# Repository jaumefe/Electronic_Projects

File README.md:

# Electronic_Projects
At this file, there will be included some electronic projects which could be used for home automation. Here, we can find the list of projects done until now:
* Weather Forecast Station

## Weather Forecast
It consists of a station which includes two sensors:
* SHT40-AD1B-R2: Temperature and Humidity Sensor
* DPS310: Barometric Pressure Sensor

This project only contains a board with both sensors which should be connected to a MCU by a I2C serial interface. In this case, I will be using a Raspberry Pi Pico to do the project. If you are also interested on the code, please check the following repository: https://github.com/jaumefe/Raspberry_Pico/tree/main/Weather_Forecast

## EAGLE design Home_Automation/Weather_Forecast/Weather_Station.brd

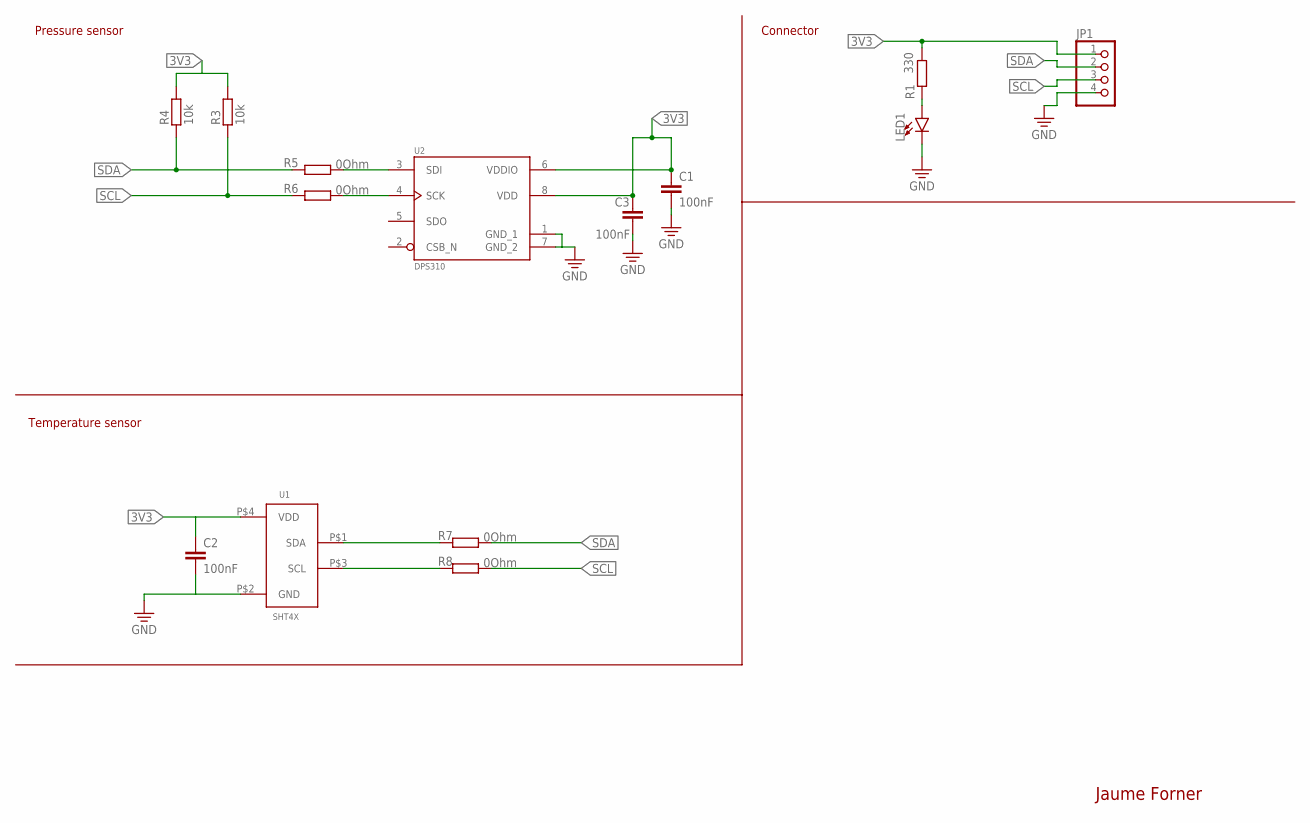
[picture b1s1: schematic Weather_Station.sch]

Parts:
C1, C2, C3: 100nF; C0603K
JP1: PINHD-1X4; 1X04
LED1: LED0603; LED-0603
R1: 330; R0603
R3, R4: 10k; R0603
R5, R6, R7, R8: 0Ohm; R0603
U1: SHT4X; SHT40-SHT41
U2: DPS310; LGA8S145X65P2X4_200X250X110-V

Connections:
3V3: C1.1, C2.1, C3.1, JP1.1, R1.1, R3.2, R4.2, U1.P$4 (VDD), U2.6 (VDDIO), U2.8 (VDD)
GND: C1.2, C2.2, C3.2, JP1.4, LED1.C, U1.P$2 (GND), U2.1 (GND_1), U2.7 (GND_2)
unnamed: R6.1, U2.4 (SCK)
unnamed: R5.1, U2.3 (SDI)
unnamed: R7.2, U1.P$1 (SDA)
unnamed: R8.2, U1.P$3 (SCL)
unnamed: LED1.A, R1.2
SCL: JP1.3, R3.1, R6.2, R8.1
SDA: JP1.2, R4.1, R5.2, R7.1

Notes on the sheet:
Jaume Forner
Pressure sensor
Temperature sensor
Connector

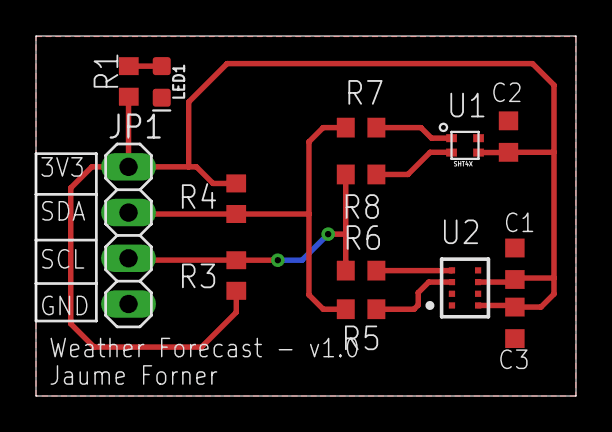
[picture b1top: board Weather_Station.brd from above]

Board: 2 copper layers, 30.0 x 20.0 mm, 14 parts (0 on the bottom side), 9 nets.

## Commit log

2022-08-30 Weather Forecast Hardware Project. Design of schematic and PCB on Eagle
2022-08-30 README file updated
2023-08-02 New version: Re-design for better working and added a LED for indicating power

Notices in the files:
parts and their libraries:
SparkFun-LED: Licensing: Creative Commons ShareAlike 4.0 International - https://creativecommons.org/licenses/by-sa/4.0
